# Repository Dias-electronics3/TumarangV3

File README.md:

# TumarangV3
Program ini merupakan pengembangan dari TumarangV2, di mana program dan hasil akhirnya memperbaiki dari kesalahan/kekurangan yang sudah dilakukan sebelumnya di TumarangV2 sebelumnya. Dengan Dokumentasi program yang lebih struktural dan desain PCB yang lebih baik. ini merupakan Final dari Tumarang yang sudah disempurnakan tanpa adanya bug.

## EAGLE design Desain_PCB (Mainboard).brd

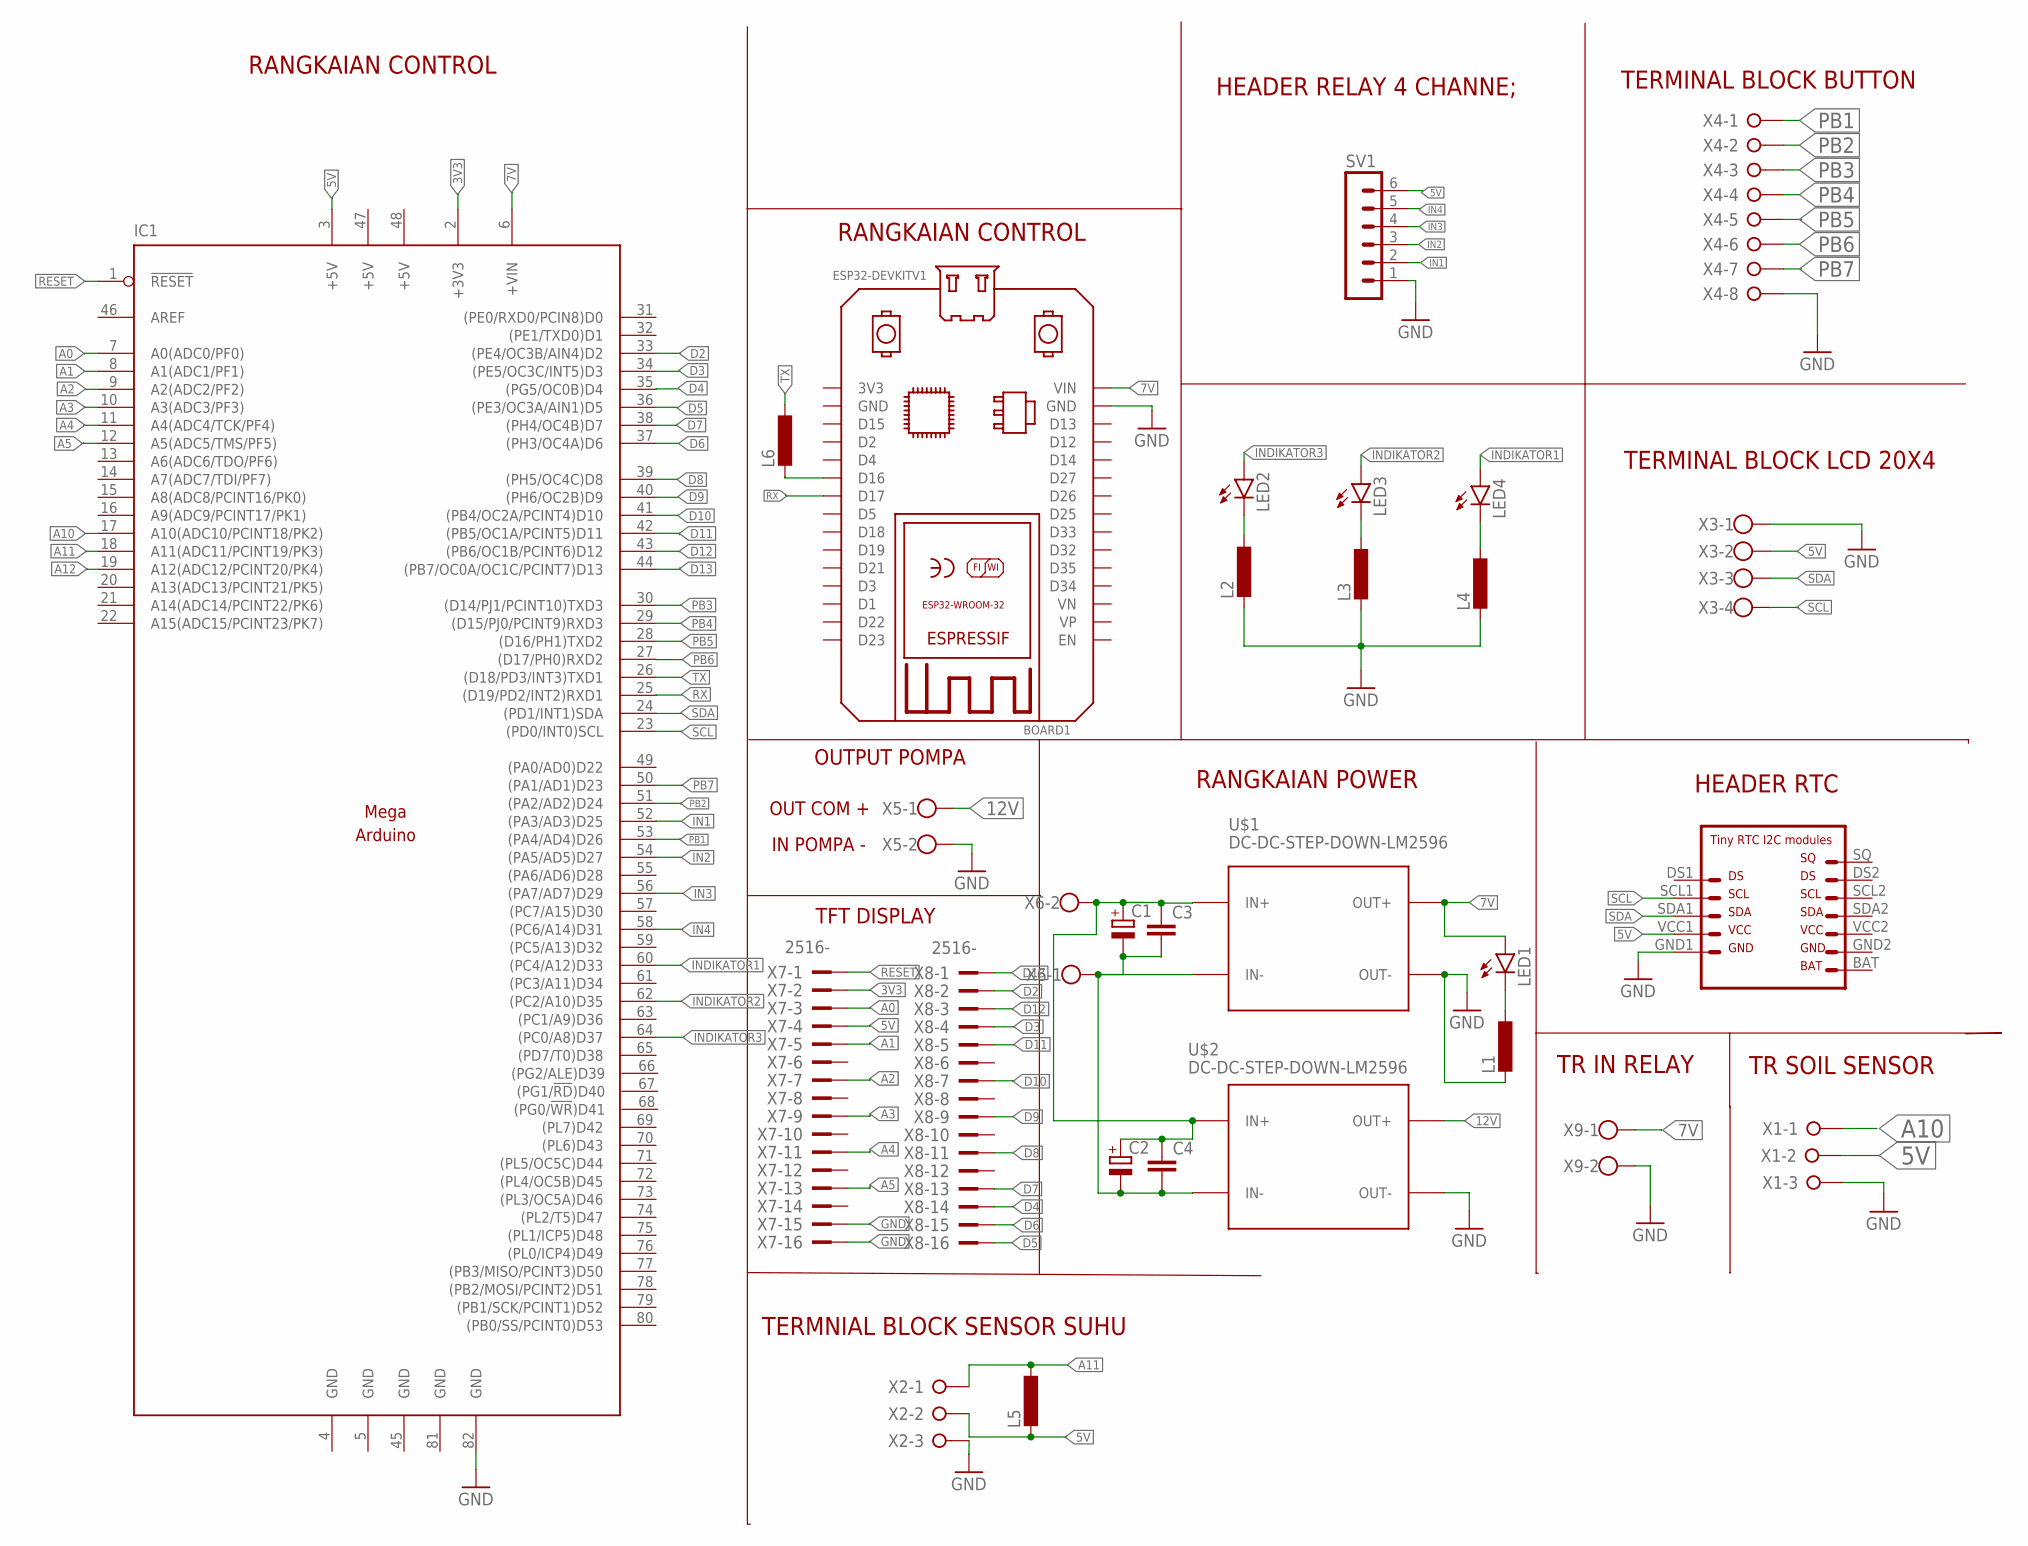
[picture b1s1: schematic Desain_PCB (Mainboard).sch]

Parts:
BOARD1: ESP32DEVKITV1; ESP32-DEVKITV1
C1, C2: CPOL-EUE2,5-6E; E2,5-6E
C3, C4: C-EU025-025X050; C025-025X050
IC1: ARDUINOMEGA
L1, L2, L3, L4, L5, L6: L-EU0207/10; 0207/10
LED1, LED2, LED3, LED4: LED5MM
SV1: MA06-1
U$1, U$2: DC-DC-STEP-DOWN-LM2596
U$3: RTC
X1, X2: W237-3E
X3: W237-4
X4: W237-08P; W237-8P
X5, X6, X9: W237-102
X7, X8: 2516-; PAK100/2500-16

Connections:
3V3: IC1.2 (+3V3), X7.2
5V: IC1.3 (+5V), L5.2, SV1.6, U$3.VCC1, X1.2, X2.2, X3.2, X7.4
7V: BOARD1.VIN, IC1.6 (+VIN), LED1.A, U$1.OUT+, X9.1
12V: U$2.OUT+, X5.1
+5V: IC1.47 (+5V), IC1.48 (+5V)
A0: IC1.7 (A0(ADC0/PF0)), X7.3
A1: IC1.8 (A1(ADC1/PF1)), X7.5
A2: IC1.9 (A2(ADC2/PF2)), X7.7
A3: IC1.10 (A3(ADC3/PF3)), X7.9
A4: IC1.11 (A4(ADC4/TCK/PF4)), X7.11
A5: IC1.12 (A5(ADC5/TMS/PF5)), X7.13
A10: IC1.17 (A10(ADC10/PCINT18/PK2)), X1.1
A11: IC1.18 (A11(ADC11/PCINT19/PK3)), L5.1, X2.1
A12: IC1.19 (A12(ADC12/PCINT20/PK4))
D2: IC1.33 ((PE4/OC3B/AIN4)D2), X8.2
D3: IC1.34 ((PE5/OC3C/INT5)D3), X8.4
D4: IC1.35 ((PG5/OC0B)D4), X8.14
D5: IC1.36 ((PE3/OC3A/AIN1)D5), X8.16
D6: IC1.37 ((PH3/OC4A)D6), X8.15
D7: IC1.38 ((PH4/OC4B)D7), X8.13
D8: IC1.39 ((PH5/OC4C)D8), X8.11
D9: IC1.40 ((PH6/OC2B)D9), X8.9
D10: IC1.41 ((PB4/OC2A/PCINT4)D10), X8.7
D11: IC1.42 ((PB5/OC1A/PCINT5)D11), X8.5
D12: IC1.43 ((PB6/OC1B/PCINT6)D12), X8.3
D13: IC1.44 ((PB7/OC0A/OC1C/PCINT7)D13), X8.1
GND: BOARD1.GND, IC1.4 (GND), IC1.5 (GND), IC1.45 (GND), IC1.81 (GND), IC1.82 (GND), L1.2, L2.2, L3.2, L4.2, SV1.1, U$1.OUT-, U$2.OUT-, U$3.GND1, X1.3, X2.3, X3.1, X4.8, X5.2, X7.15, X7.16, X9.2
IN1: IC1.52 ((PA3/AD3)D25), SV1.2
IN2: IC1.54 ((PA5/AD5)D27), SV1.3
IN3: IC1.56 ((PA7/AD7)D29), SV1.4
IN4: IC1.58 ((PC6/A14)D31), SV1.5
INDIKATOR1: IC1.60 ((PC4/A12)D33), LED4.A
INDIKATOR2: IC1.62 ((PC2/A10)D35), LED3.A
INDIKATOR3: IC1.64 ((PC0/A8)D37), LED2.A
unnamed: C1.-, C2.-, C3.2, C4.2, U$1.IN-, U$2.IN-, X6.1
unnamed: L1.1, LED1.K (C)
unnamed: BOARD1.D16, L6.2
unnamed: L2.1, LED2.K (C)
unnamed: L3.1, LED3.K (C)
unnamed: L4.1, LED4.K (C)
unnamed: C1.+, C2.+, C3.1, C4.1, U$1.IN+, U$2.IN+, X6.2
PB1: IC1.53 ((PA4/AD4)D26), X4.1
PB2: IC1.51 ((PA2/AD2)D24), X4.2
PB3: IC1.30 ((D14/PJ1/PCINT10)TXD3), X4.3
PB4: IC1.29 ((D15/PJ0/PCINT9)RXD3), X4.4
PB5: IC1.28 ((D16/PH1)TXD2), X4.5
PB6: IC1.27 ((D17/PH0)RXD2), X4.6
PB7: IC1.50 ((PA1/AD1)D23), X4.7
RESET: IC1.1 (!RESET), X7.1
RX: BOARD1.D17, IC1.25 ((D19/PD2/INT2)RXD1)
SCL: IC1.23 ((PD0/INT0)SCL), U$3.SCL1, X3.4
SDA: IC1.24 ((PD1/INT1)SDA), U$3.SDA1, X3.3
TX: IC1.26 ((D18/PD3/INT3)TXD1), L6.1

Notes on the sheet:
HEADER RELAY 4 CHANNE;
TR SOIL SENSOR
TERMNIAL BLOCK SENSOR SUHU
TERMINAL BLOCK LCD 20X4
HEADER RTC
RANGKAIAN POWER
TERMINAL BLOCK BUTTON
RANGKAIAN CONTROL
OUTPUT POMPA
OUT COM +
IN POMPA -
TFT DISPLAY
TR IN RELAY

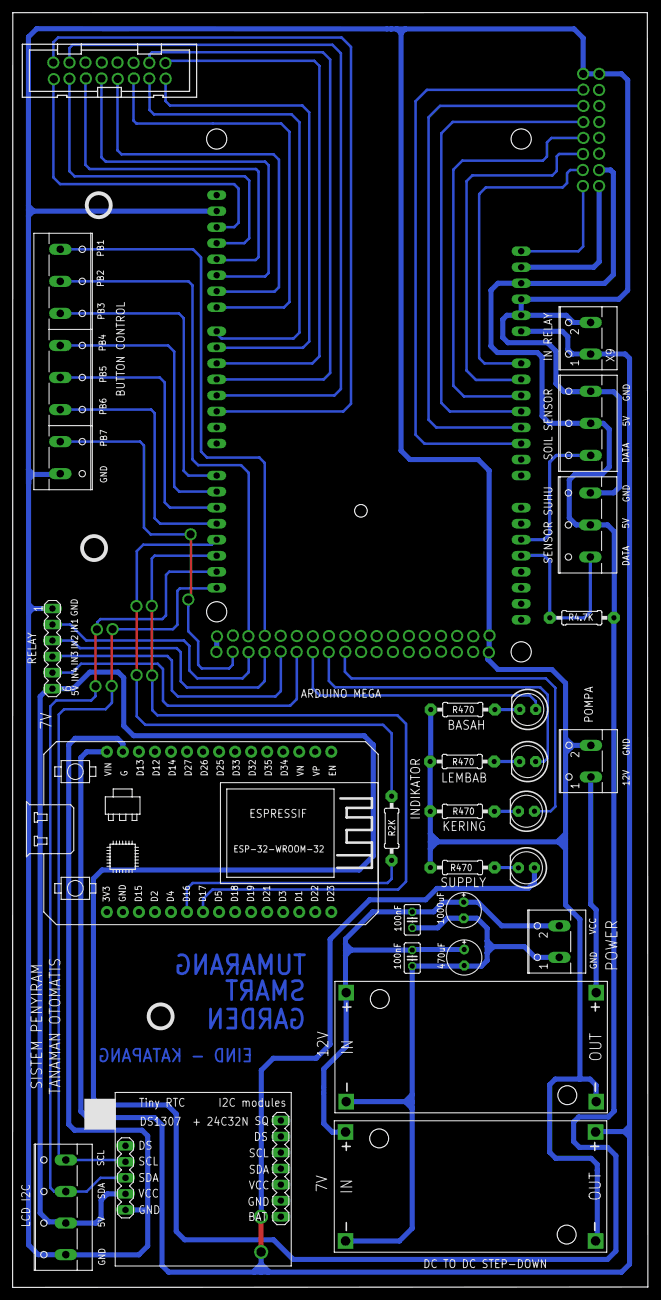
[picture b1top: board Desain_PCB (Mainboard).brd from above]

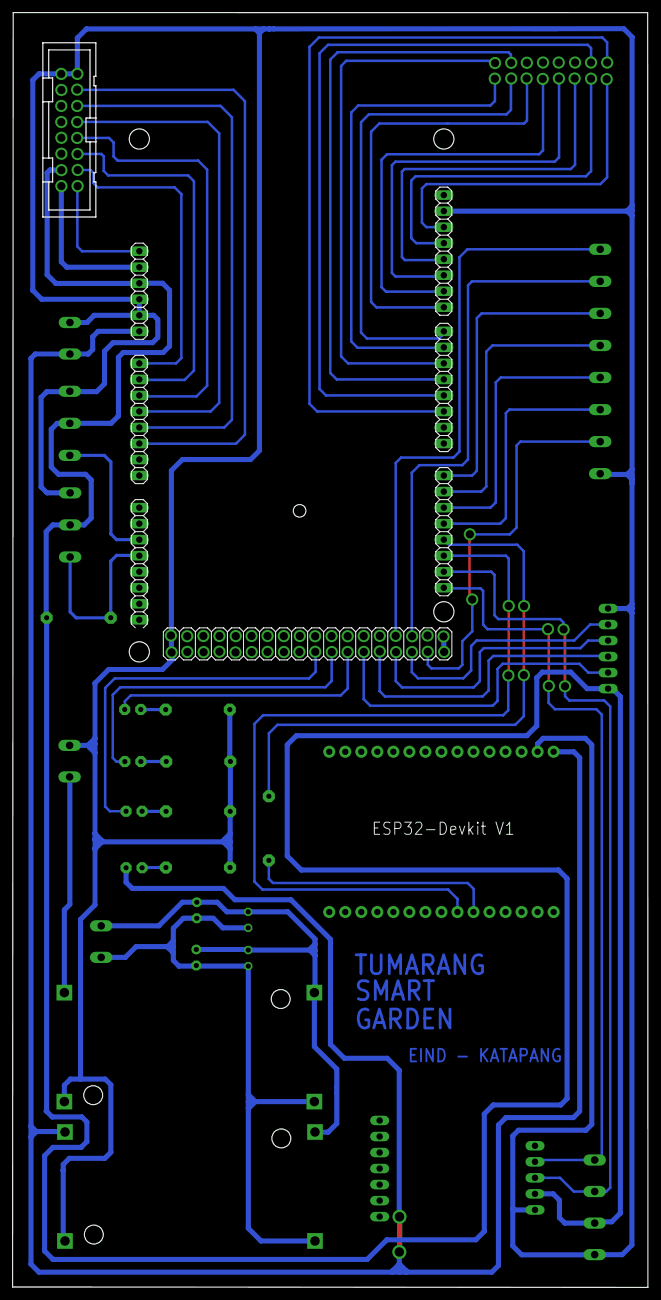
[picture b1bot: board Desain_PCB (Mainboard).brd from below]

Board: 2 copper layers, 100.7 x 202.0 mm, 29 parts (2 on the bottom side), 52 nets.

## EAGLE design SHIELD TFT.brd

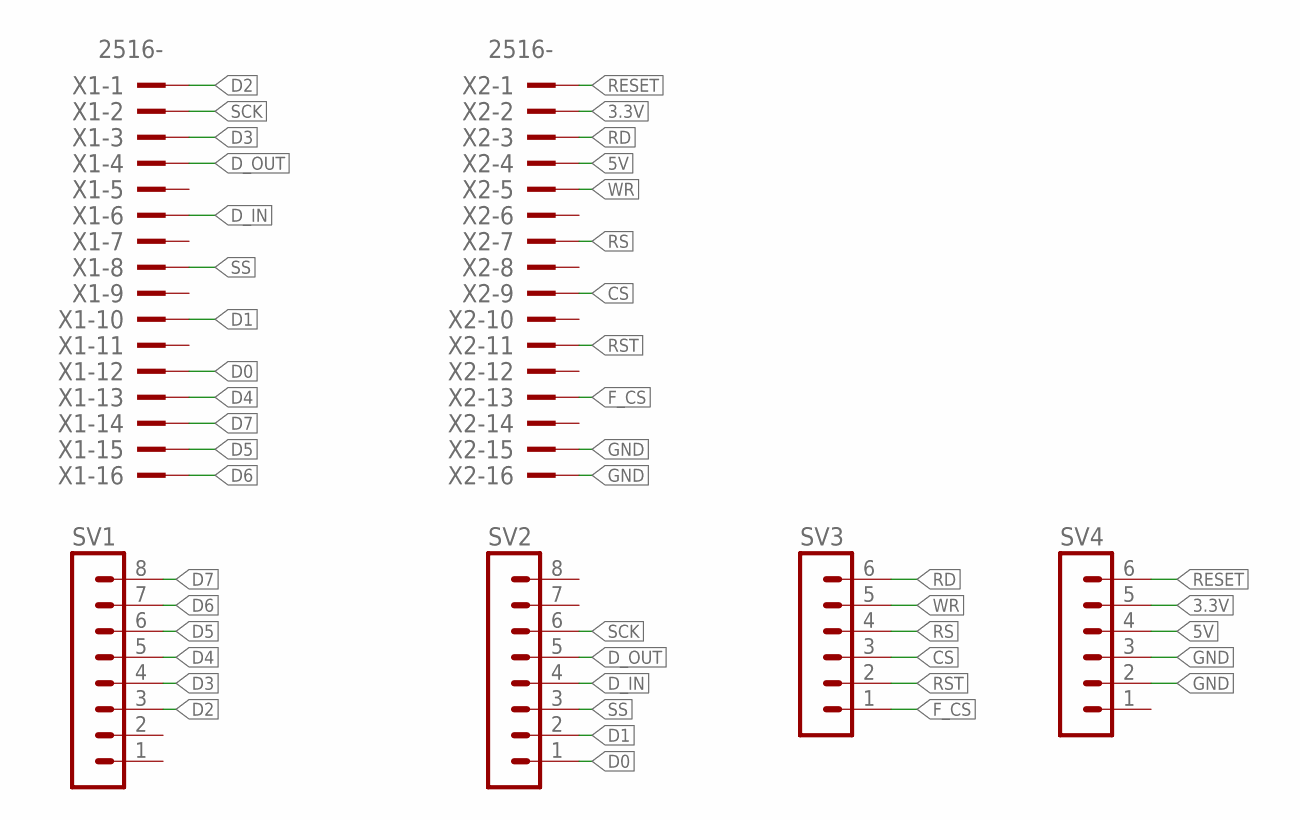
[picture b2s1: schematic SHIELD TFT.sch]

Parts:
SV1, SV2: MA08-1
SV3, SV4: MA06-1
X1, X2: 2516-; PAK100/2500-16

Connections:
3.3V: SV4.5, X2.2
5V: SV4.4, X2.4
CS: SV3.3, X2.9
D0: SV2.1, X1.12
D1: SV2.2, X1.10
D2: SV1.3, X1.1
D3: SV1.4, X1.3
D4: SV1.5, X1.13
D5: SV1.6, X1.15
D6: SV1.7, X1.16
D7: SV1.8, X1.14
D_IN: SV2.4, X1.6
D_OUT: SV2.5, X1.4
F_CS: SV3.1, X2.13
GND: SV4.2, SV4.3, X2.15, X2.16
RD: SV3.6, X2.3
RESET: SV4.6, X2.1
RS: SV3.4, X2.7
RST: SV3.2, X2.11
SCK: SV2.6, X1.2
SS: SV2.3, X1.8
WR: SV3.5, X2.5

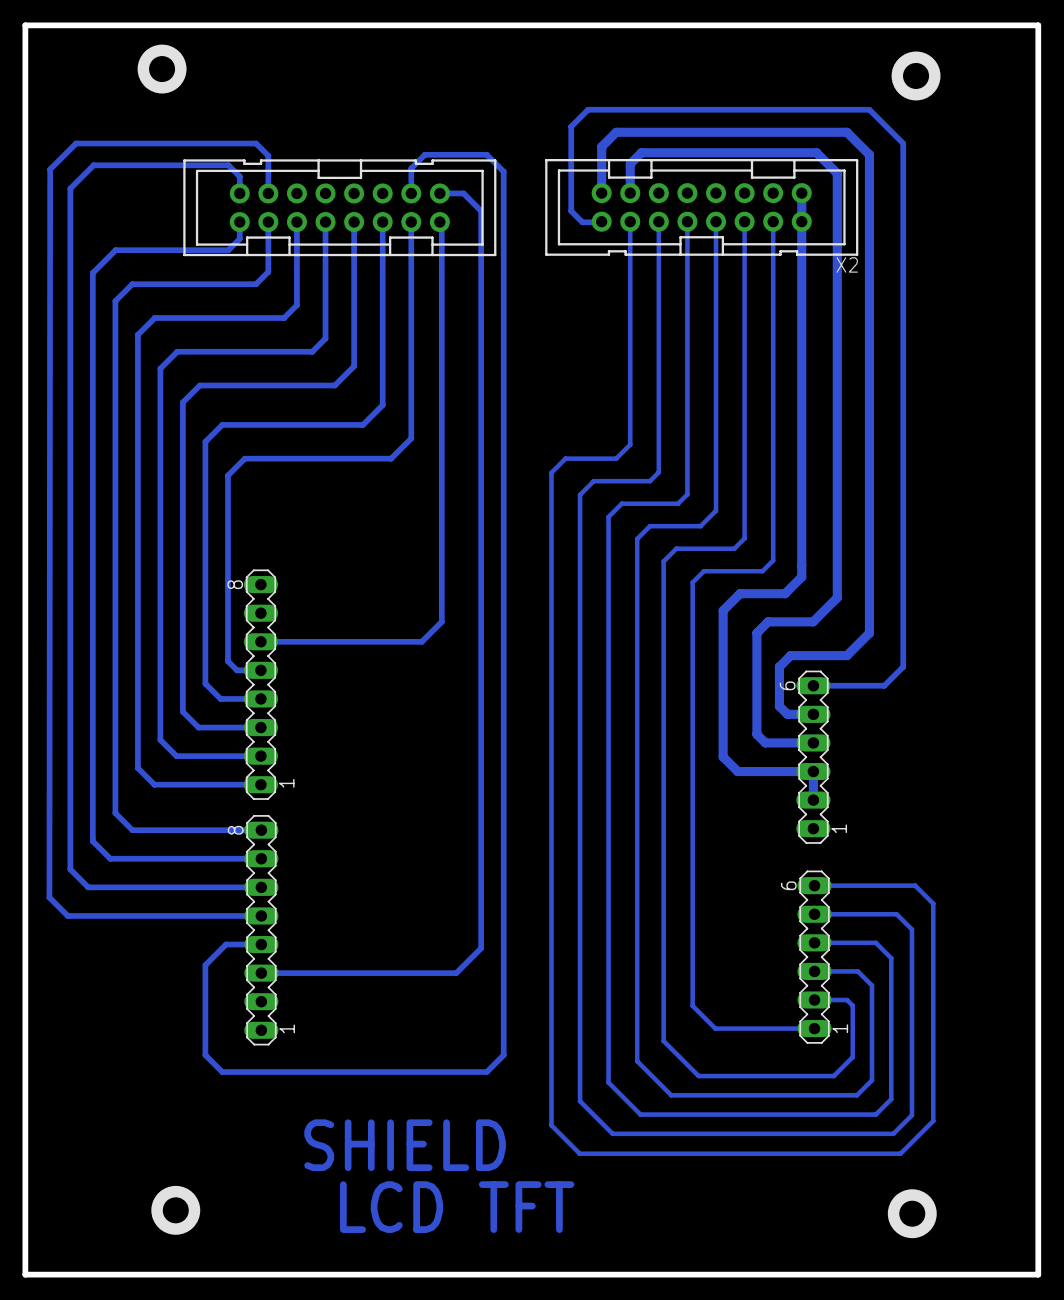
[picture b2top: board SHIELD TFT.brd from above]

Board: 2 copper layers, 90.0 x 111.0 mm, 6 parts (0 on the bottom side), 22 nets.

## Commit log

2025-12-07 Add files via upload
    Setiap logika program mulai dari penamaan variabel yang digunakan, logika display TFT, logika kontroll Pompa, komunikasi serial dengan ESP32, dan penyimpanan Memory ke EEPROM sudah dibagi dalam beber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
2025-12-07 Add files via upload
    Desain Shield LCD TFT (Schematic & Lay out) (Eagle Autodesk)
2025-12-14 Add files via upload
    ini adalah Desain PCB untuk digunakan dalam proses pembuatan TumarangV3 untuk menempatkan semua komponen utama (Arduino Mega 2560 dan ESP32 Devkit V1)
2025-12-23 Add files via upload
    Ini Adalah program penghubung antara Logika kontrol dari Arduino Mega -> Esp32 Devkit V1 -> Firebase (Program ini berada di Esp32)

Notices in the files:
parts and their libraries:
diy-modules: Released under the Creative Commons Attribution 4.0 International License: http://creativecommons.org/licenses/by/4.0
